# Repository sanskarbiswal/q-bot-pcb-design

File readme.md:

# Q-Bot PCB

## Auto-generate Gerber Files

1. Open Python Terminal from KiCad\bin\
2. ```$ python path_to_repo\Scripting\t1.py path_to_repo\Bot_Controller.kicad_pcb```
3. Find The Generated Plot Files in /Plot Folder

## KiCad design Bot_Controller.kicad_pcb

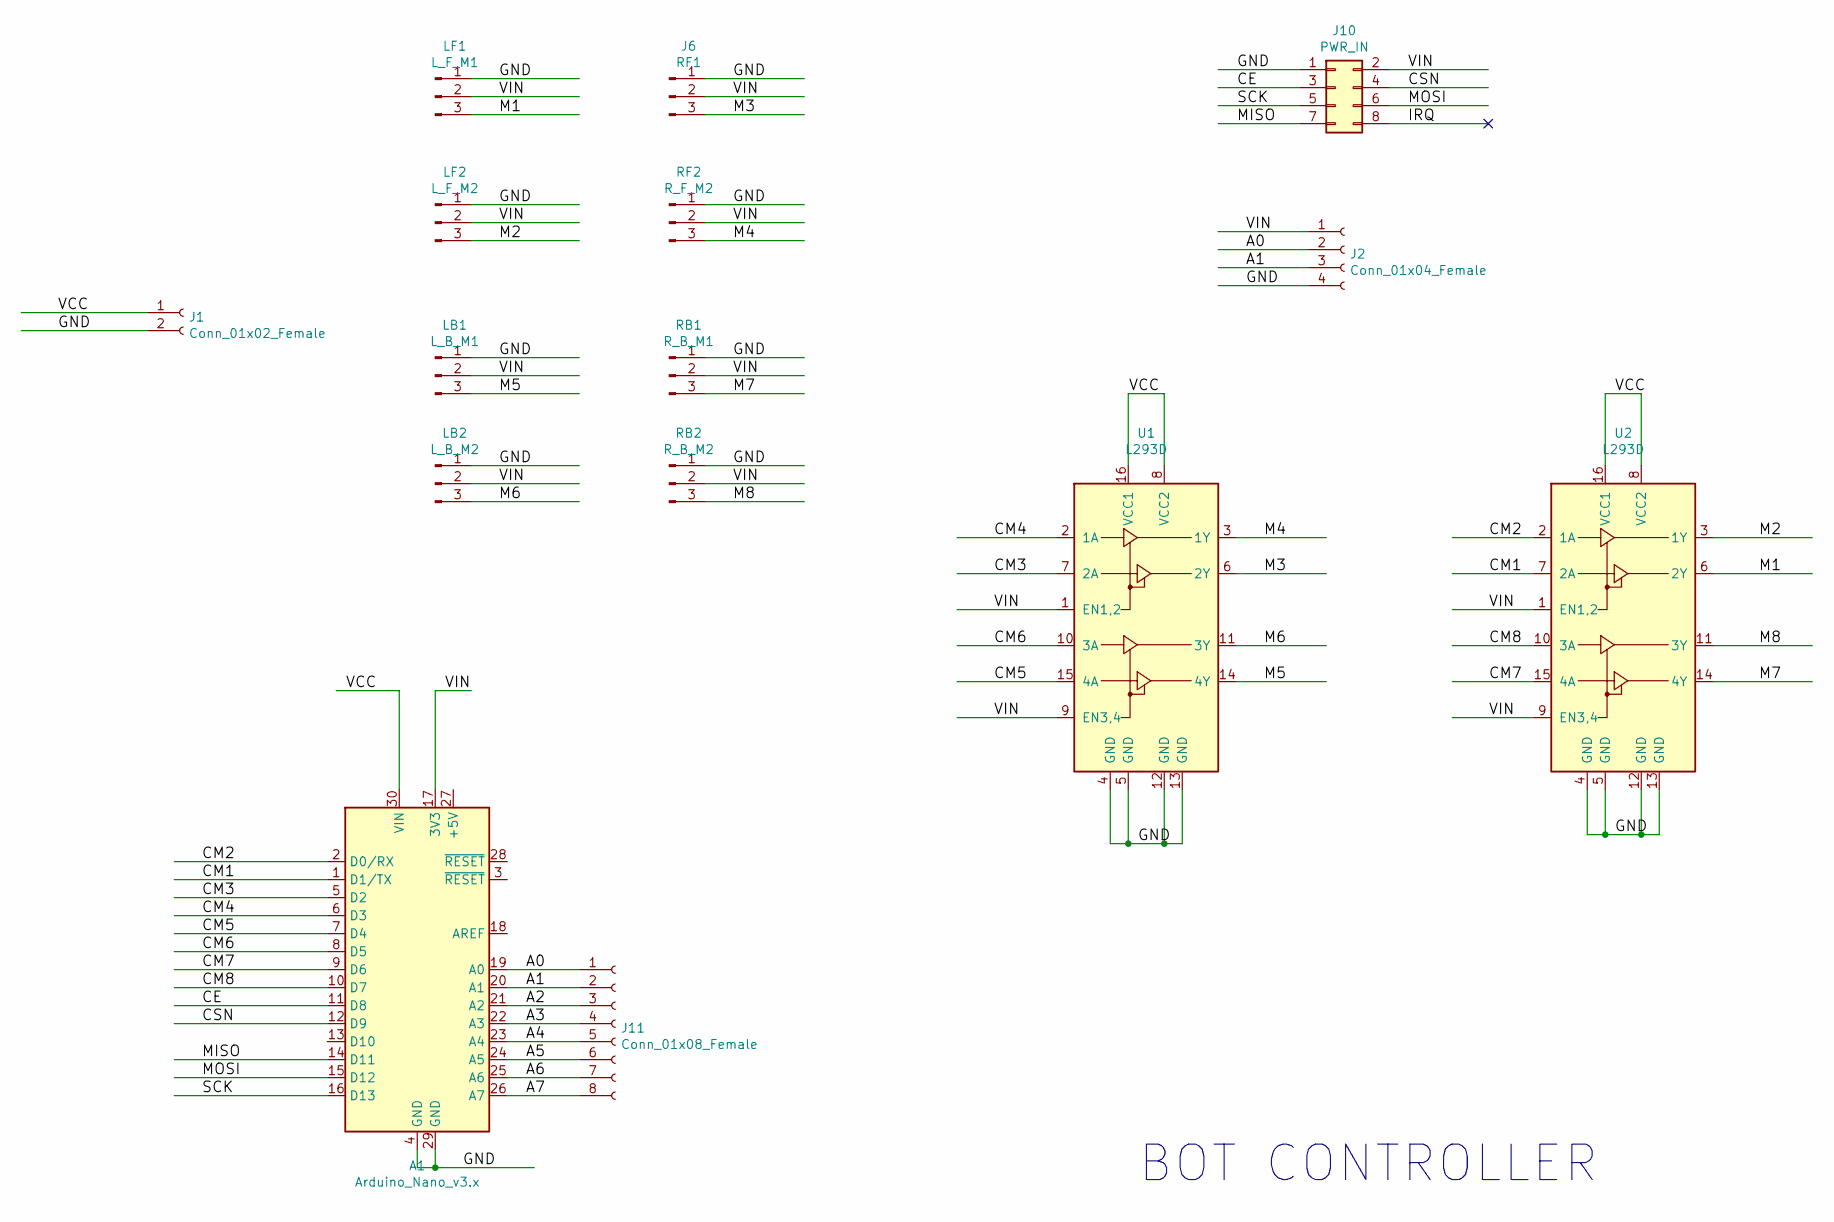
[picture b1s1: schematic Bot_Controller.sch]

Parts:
A1: Arduino_Nano_v3.x; Arduino_Nano
J1: Conn_01x02_Female; PinHeader_1x02_P2.54mm_Vertical
J2: Conn_01x04_Female; PinHeader_1x04_P2.54mm_Vertical
J6: RF1; PinHeader_1x03_P2.54mm_Vertical
J10: PWR_IN; PinHeader_2x04_P2.54mm_Vertical
J11: Conn_01x08_Female; PinHeader_1x08_P2.54mm_Vertical
LB1: L_B_M1; PinHeader_1x03_P2.54mm_Vertical
LB2: L_B_M2; PinHeader_1x03_P2.54mm_Vertical
LF1: L_F_M1; PinHeader_1x03_P2.54mm_Vertical
LF2: L_F_M2; PinHeader_1x03_P2.54mm_Vertical
RB1: R_B_M1; PinHeader_1x03_P2.54mm_Vertical
RB2: R_B_M2; PinHeader_1x03_P2.54mm_Vertical
RF2: R_F_M2; PinHeader_1x03_P2.54mm_Vertical
U1, U2: L293D; DIP-16_W7.62mm

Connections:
/A0: A1.19 (A0), J2.2, J11.1
/A1: A1.20 (A1), J2.3, J11.2
/A2: A1.21 (A2), J11.3
/A3: A1.22 (A3), J11.4
/A4: A1.23 (A4), J11.5
/A5: A1.24 (A5), J11.6
/A6: A1.25 (A6), J11.7
/A7: A1.26 (A7), J11.8
/CE: A1.11 (D8), J10.3
/CM1: A1.1 (D1/TX), U2.7 (2A)
/CM2: A1.2 (D0/RX), U2.2 (1A)
/CM3: A1.5 (D2), U1.7 (2A)
/CM4: A1.6 (D3), U1.2 (1A)
/CM5: A1.7 (D4), U1.15 (4A)
/CM6: A1.8 (D5), U1.10 (3A)
/CM7: A1.9 (D6), U2.15 (4A)
/CM8: A1.10 (D7), U2.10 (3A)
/CSN: A1.12 (D9), J10.4
/GND: A1.4 (GND), A1.29 (GND), J1.2, J2.4, J6.1, J10.1, LB1.1, LB2.1, LF1.1, LF2.1, RB1.1, RB2.1, RF2.1, U1.4 (GND), U1.5 (GND), U1.12 (GND), U1.13 (GND), U2.4 (GND), U2.5 (GND), U2.12 (GND), U2.13 (GND)
/IRQ: J10.8
/M1: LF1.3, U2.6 (2Y)
/M2: LF2.3, U2.3 (1Y)
/M3: J6.3, U1.6 (2Y)
/M4: RF2.3, U1.3 (1Y)
/M5: LB1.3, U1.14 (4Y)
/M6: LB2.3, U1.11 (3Y)
/M7: RB1.3, U2.14 (4Y)
/M8: RB2.3, U2.11 (3Y)
/MISO: A1.14 (D11), J10.7
/MOSI: A1.15 (D12), J10.6
/SCK: A1.16 (D13), J10.5
/VCC: A1.30 (VIN), J1.1, U1.8 (VCC2), U1.16 (VCC1), U2.8 (VCC2), U2.16 (VCC1)
/VIN: A1.17 (3V3), J2.1, J6.2, J10.2, LB1.2, LB2.2, LF1.2, LF2.2, RB1.2, RB2.2, RF2.2, U1.1 (EN1,2), U1.9 (EN3,4), U2.1 (EN1,2), U2.9 (EN3,4)

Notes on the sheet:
BOT CONTROLLER

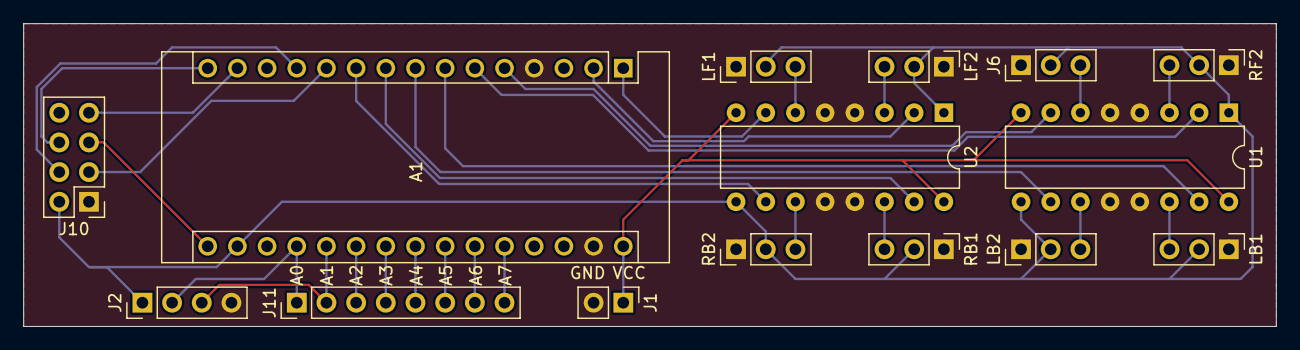
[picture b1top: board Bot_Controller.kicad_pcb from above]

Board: 2 copper layers, 107.2 x 25.9 mm, 15 parts (0 on the bottom side), 32 nets.

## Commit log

2020-11-15 Added Plots
